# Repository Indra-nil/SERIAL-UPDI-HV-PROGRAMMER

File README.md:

# Serial UPDI HV Programmer

Serial UPDI HV Programmer for new AVR ICs using Silabs CP2105 IC. Because of having two UART core one is dedicated to UPDI and another is for Serial communication. No need for two seperate usb port for two UART anymore.

when Vcc selected Vout nearly 4.7v

when +3.3v selected Vout 3.3v

when EXT selected Vout external voltage from target board

Some useful links
--------------------

[pyupdi](https://github.com/mraardvark/pyupdi.git)

[MegaCoreX(arduino core)](https://github.com/MCUdude/MegaCoreX.git)

[megaTinyCore(arduino core)](https://github.com/SpenceKonde/megaTinyCore.git)

[DxCore(arduino core)](https://github.com/SpenceKonde/DxCore.git)

[TinyCore(arduino core)](https://github.com/xukangmin/TinyCore.git)

[Microchip Studio for AVR](https://www.microchip.com/en-us/tools-resources/develop/microchip-studio)

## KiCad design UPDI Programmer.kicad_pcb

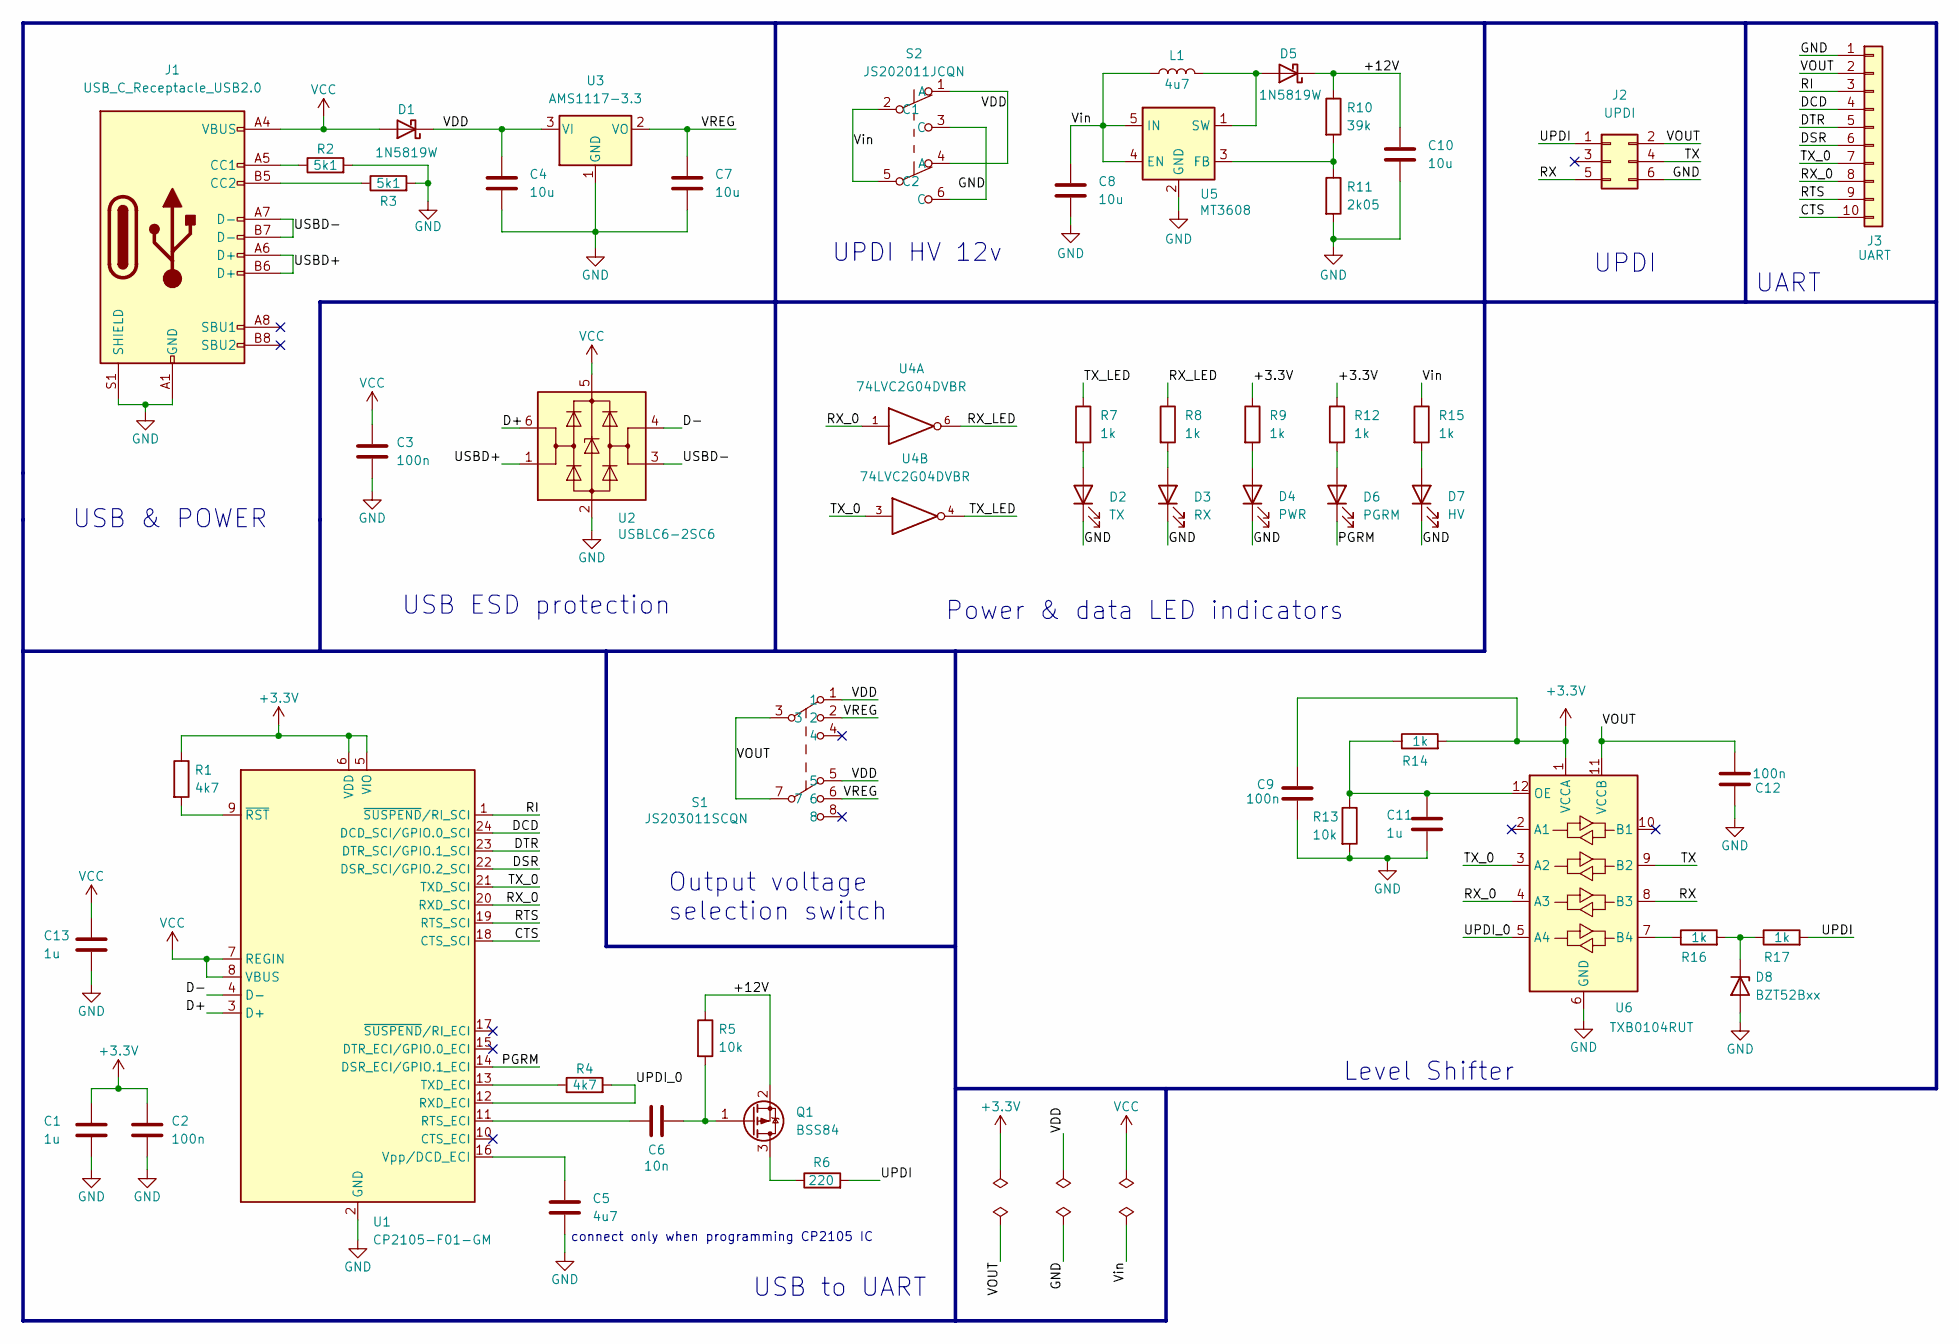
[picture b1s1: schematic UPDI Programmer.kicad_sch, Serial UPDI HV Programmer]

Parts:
C1, C11, C13: 1u; C_0603_1608Metric
C2, C3, C9, C12: 100n; C_0603_1608Metric
C4, C7, C8, C10: 10u; C_0805_2012Metric
C5: 4u7; C_0603_1608Metric
C6: 10n; C_0603_1608Metric
D1, D5: 1N5819W; D_SOD-123
D2: TX; LED_0603_1608Metric
D3: RX; LED_0603_1608Metric
D4: PWR; LED_0603_1608Metric
D6: PGRM; LED_0603_1608Metric
D7: HV; LED_0603_1608Metric
D8: BZT52Bxx; D_SOD-323_HandSoldering
J1: USB_C_Receptacle_USB2.0; HRO_TYPE-C-31-M-12
J2: UPDI; IDC-Header_2x03_P2.54mm_Vertical
J3: UART; PinHeader_1x10_P2.54mm_Vertical
L1: 4u7; L_0805_2012Metric
Q1: BSS84; SOT-23
R1, R4: 4k7; R_0603_1608Metric
R2, R3: 5k1; R_0603_1608Metric
R5, R13: 10k; R_0603_1608Metric
R6: 220; R_0603_1608Metric
R7, R8, R9, R12, R14, R15, R16, R17: 1k; R_0603_1608Metric
R10: 39k; R_0603_1608Metric
R11: 2k05; R_0603_1608Metric
S1: JS203011SCQN; Manufacturer_Part_Number JS203011SCQN; Mouser Part Number 611-JS203011SCQN
S2: JS202011JCQN; Manufacturer_Part_Number JS202011JCQN; Mouser Part Number 611-JS202011JCQN
U1: CP2105-F01-GM; Manufacturer_Part_Number CP2105-F01-GM
U2: USBLC6-2SC6; SOT-23-6
U3: AMS1117-3.3; SOT-89-3
U4: 74LVC2G04DVBR; SOT-23-6
U5: MT3608; SOT-23-6
U6: TXB0104RUT; Texas_R_PUQFN-N12

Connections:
+3.3V: C1.1, C2.1, C9.2, R1.1, R9.1, R12.1, R14.2, U1.5 (VIO), U1.6 (VDD), U6.1 (VCCA)
/+12V: C10.1, D5.1 (K), Q1.2 (S), R5.1, R10.1
/CTS: J3.10, U1.18 (CTS_SCI)
/D+: U1.3 (D+), U2.6 (I/O1)
/D-: U1.4 (D-), U2.4 (I/O2)
/DCD: J3.4, U1.24 (DCD_SCI/GPIO.0_SCI)
/DSR: J3.6, U1.22 (DSR_SCI/GPIO.2_SCI)
/DTR: J3.5, U1.23 (DTR_SCI/GPIO.1_SCI)
/PGRM: D6.1 (K), U1.14 (DSR_ECI/GPIO.1_ECI)
/RI: J3.3, U1.1 (~SUSPEND/RI_SCI)
/RTS: J3.9, U1.19 (RTS_SCI)
/RX: J2.5, U6.8 (B3)
/RX_0: J3.8, U1.20 (RXD_SCI), U4.1, U6.4 (A3)
/RX_LED: R8.1, U4.6
/TX: J2.4, U6.9 (B2)
/TX_0: J3.7, U1.21 (TXD_SCI), U4.3, U6.3 (A2)
/TX_LED: R7.1, U4.4
/UPDI: J2.1, R6.2, R17.2
/UPDI_0: R4.2, U1.12 (RXD_ECI), U6.5 (A4)
/USBD+: J1.A6 (D+), J1.B6 (D+), U2.1 (I/O1)
/USBD-: J1.A7 (D-), J1.B7 (D-), U2.3 (I/O2)
/VDD: C4.1, D1.1 (K), S1.1, S1.5, S2.1 (A), S2.4 (A), U3.3 (VI)
/VOUT: C12.1, J2.2, J3.2, S1.3, S1.7, U6.11 (VCCB)
/VREG: C7.1, S1.2, S1.6, U3.2 (VO)
/Vin: C8.1, L1.1, R15.1, S2.2 (C1), S2.5 (C2), U5.4 (EN), U5.5 (IN)
GND: C1.2, C2.2, C3.2, C4.2, C5.2, C7.2, C8.2, C9.1, C10.2, C11.1, C12.2, C13.2, D2.1 (K), D3.1 (K), D4.1 (K), D7.1 (K), D8.2 (A), J1.A1 (GND), J1.A12 (GND), J1.B1 (GND), J1.B12 (GND), J1.S1 (SHIELD), J2.6, J3.1, R2.2, R3.2, R11.2, R13.2, S2.3 (C), S2.6 (C), U1.2 (GND), U1.25 (GND), U2.2 (GND), U3.1 (GND), U4.2 (GND), U5.2 (GND), U6.6 (GND)
unnamed: C5.1, U1.16 (Vpp/DCD_ECI)
unnamed: C6.1, U1.11 (RTS_ECI)
unnamed: C6.2, Q1.1 (G), R5.2
unnamed: C11.2, R13.1, R14.1, U6.12 (OE)
unnamed: D2.2 (A), R7.2
unnamed: D3.2 (A), R8.2
unnamed: D4.2 (A), R9.2
unnamed: D5.2 (A), L1.2, U5.1 (SW)
unnamed: D6.2 (A), R12.2
unnamed: D7.2 (A), R15.2
unnamed: D8.1 (K), R16.2, R17.1
unnamed: J1.A5 (CC1), R2.1
unnamed: J1.B5 (CC2), R3.1
unnamed: Q1.3 (D), R6.1
unnamed: R1.2, U1.9 (~RST)
unnamed: R4.1, U1.13 (TXD_ECI)
unnamed: R10.2, R11.1, U5.3 (FB)
unnamed: R16.1, U6.7 (B4)
VCC: C3.1, C13.1, D1.2 (A), J1.A4 (VBUS), J1.A9 (VBUS), J1.B4 (VBUS), J1.B9 (VBUS), U1.7 (REGIN), U1.8 (VBUS), U2.5 (VBUS), U4.5 (VCC)

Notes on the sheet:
Output voltage selection switch
Level Shifter
USB to UART
UPDI HV 12v
UART
connect only when programming CP2105 IC
USB ESD protection
UPDI
Power & data LED indicators
USB & POWER

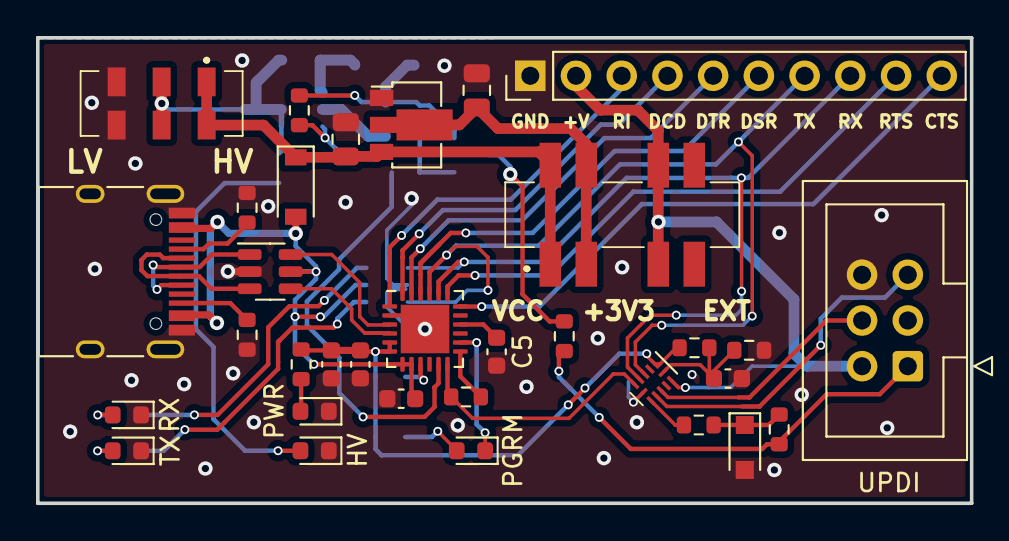
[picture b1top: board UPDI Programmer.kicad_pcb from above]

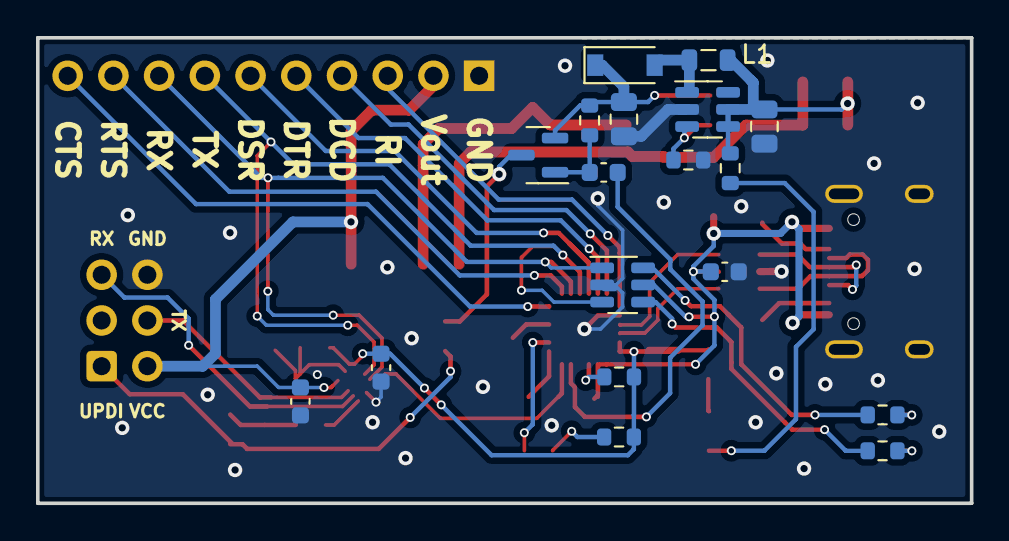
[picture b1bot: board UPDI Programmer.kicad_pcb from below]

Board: 2 copper layers, 51.9 x 25.9 mm, 51 parts (18 on the bottom side), 45 nets.

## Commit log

2022-10-10 Initial Release
